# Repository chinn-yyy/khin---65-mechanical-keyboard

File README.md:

# khin---65-mechanical-keyboard
This keyboard was designed for productivity for the Blueprint club ran by HackClub. It features a 66 key layout with 2 programmable macro keys. I chose the MMD Fairy Linear switches for this project. Not only do they sound amazing, they also match my vibe; transparent. Additionally, I decided to use some random AliExpress screw-in stabilizers that are also, you guessed it, transparent! 

My keyboard isn't just a keyboard with keys. It also features a big, bright, 0.91 inch OLED display that can display the last key you pressed, a fun animation, etc. Not only does it have an OLED it also has 68 addressable LED's. One for each key. These can be any color and any pattern.

On the firmware side of things, my keyboard is being ran by QMK open source firmware on a Raspberry Pi Pico. QMK is specifically designed for keyboards, and not only is it easy to use but it also has tons of features. 

Make sure to look at my Blueprint page to see the journal and the process it took to build this. Here is the link: https://blueprint.hackclub.com/projects/11738

Here are some photos of the finished product:

  Fully Assembled (CAD):

  Schematic:

  PCB Editor:

  CAD:

[tableConvert.com_irgoez.md](https://github.com/user-attachments/files/25429461/tableConvert.com_irgoez.md)
| Name:                             | Description:                                                        | Price: (each) | Shipping Price: | Quanity: | Manufacturer: | Total Price (with tax + shipping): | URL:                                                                                                                                                                                                                                                                                                                                                                                                                                                                                                                                                                                                                                        |
|-----------------------------------|---------------------------------------------------------------------|---------------|-----------------|----------|---------------|------------------------------------|---------------------------------------------------------------------------------------------------------------------------------------------------------------------------------------------------------------------------------------------------------------------------------------------------------------------------------------------------------------------------------------------------------------------------------------------------------------------------------------------------------------------------------------------------------------------------------------------------------------------------------------------|
| Raspberry Pi Pico w/ Headers      | 40 pin RP2040 based MCU, the brains for the keyboard. (not the offical one, proceed with caution)               | $3.41         | $0.00           | 1        | AliExpress        | $3.94                              | https://www.aliexpress.us/item/3256805941727857.html?spm=a2g0o.cart.0.0.295b38daIYYoHW&mp=1&pdp_npi=6%40dis%21USD%21USD%203.41%21USD%203.41%21%21USD%203.41%21%21%21%402103212317738723428262562e918f%2112000035881956746%21ct%21US%216916366760%21%211%210%21&_gl=1*17auvbk*_gcl_aw*R0NMLjE3NzM2MDE5MDIuQ2owS0NRandzZG5OQmhDNEFSSXNBQV8zaGVpZ1R3cW5RcFRoUlY1S0hManNRUVdXY0pHMEVsM1UtMV96MlQ0YVdkZmw2VFkyaS05Qm5lY2FBc2RWRUFMd193Y0I.*_gcl_dc*R0NMLjE3NzM2MDE5MDIuQ2owS0NRandzZG5OQmhDNEFSSXNBQV8zaGVpZ1R3cW5RcFRoUlY1S0hManNRUVdXY0pHMEVsM1UtMV96MlQ0YVdkZmw2VFkyaS05Qm5lY2FBc2RWRUFMd193Y0I.*_gcl_au*MTkwNzg4MzkyMy4xNzY5MDMzMzcx*_ga*MjkyODU0MjIxLjE3NzM4NzE3NDY.*_ga_VED1YSGNC7*czE3NzM4NzE3NDUkbzEkZzEkdDE3NzM4NzIzNDMkajU5JGwwJGgw&gatewayAdapt=glo2usa                                                                                                                                                                                                                                                                                                                                                                                                                                                                                                                                                                        |
| V2 PCB Mount Screw-in Stabilizers | Keyboard stabilizers, allows the space, shift etc. to not collapse. | $5.27         | $0.00           | 1        | AliExpress    | $6.08                              | https://www.aliexpress.us/item/3256807050530252.html?spm=a2g0o.cart.0.0.1d1938daK18Quu&mp=1&pdp_npi=6%40dis%21USD%21USD%205.58%21USD%205.27%21%21USD%205.12%21%21%21%402101eecd17715431674755596e02ab%2112000039909995531%21ct%21US%216916366760%21%211%210%21&_gl=1*1gsy9e4*_gcl_aw*R0NMLjE3Njk4MDk2MjEuQ2p3S0NBaUFqOExMQmhBa0Vpd0FKamJZNzBrTW1QMW5Fa1VGM1F0RzFFLXI5amsxQnc4dU1UNko1MWo4V3RWZ24yM1doeGZNdXJseDZob0MxLVlRQXZEX0J3RQ..*_gcl_au*MTkwNzg4MzkyMy4xNzY5MDMzMzcx*_ga*Mzk1Mzc0NzMxLjE3NzE0NTE5NjM.*_ga_VED1YSGNC7*czE3NzE1NDMxMzIkbzMkZzEkdDE3NzE1NDMzMzckajQyJGwwJGgw&gatewayAdapt=glo2usa                                        |
| MMD Fairy Switch Linear           | Clear keyboard switches, buttons. Pack of 70.                       | $32.57        | $0.00           | 1        | AliExpress    | $37.59                             | https://www.aliexpress.us/item/3256805623892710.html?src=google&pdp_npi=4%40dis%21USD%2114.90%2113.71%21%21%21%21%21%40%2112000034431152527%21ppc%21%21%21&gatewayAdapt=glo2usa                                                                                                                                                                                                                                                                                                                                                                                                                                                             |
| 1N4148 Switching Diode            | Used in the keyboard matrix to prevent ghosting. Pack of 50.        | $1.23         | $0.00           | 2        | AliExpress    | $2.84                              | https://www.aliexpress.us/item/3256806058794623.html?spm=a2g0o.cart.0.0.1d1938daMNUGBd&mp=1&pdp_npi=6%40dis%21USD%21USD%201.79%21USD%201.23%21%21USD%201.07%21%21%21%402101eecd17713708062508328e02a6%2112000036448323916%21ct%21US%216916366760%21%212%210%21&_gl=1*5igzdr*_gcl_aw*R0NMLjE3Njk4MDk2MjEuQ2p3S0NBaUFqOExMQmhBa0Vpd0FKamJZNzBrTW1QMW5Fa1VGM1F0RzFFLXI5amsxQnc4dU1UNko1MWo4V3RWZ24yM1doeGZNdXJseDZob0MxLVlRQXZEX0J3RQ..*_gcl_au*MTkwNzg4MzkyMy4xNzY5MDMzMzcx*_ga*NDk1NTA1MDMwLjE3NzEzNjg0MzM.*_ga_VED1YSGNC7*czE3NzEzNjg0MzIkbzEkZzEkdDE3NzEzNzEwMTUkajU5JGwwJGgw&gatewayAdapt=glo2usa                                         |
| SK6812 MINI-E RGB                 | Addressable LED's for the keyboard. Pack of 100.                    | $6.03         | $0.00           | 1        | AliExpress    | $6.96                              | https://www.aliexpress.us/item/3256805007401420.html?spm=a2g0o.cart.0.0.1d1938daMNUGBd&mp=1&pdp_npi=6%40dis%21USD%21USD%206.42%21USD%206.03%21%21USD%205.32%21%21%21%402101eecd17713708062508328e02a6%2112000032072424635%21ct%21US%216916366760%21%211%210%21&_gl=1*5igzdr*_gcl_aw*R0NMLjE3Njk4MDk2MjEuQ2p3S0NBaUFqOExMQmhBa0Vpd0FKamJZNzBrTW1QMW5Fa1VGM1F0RzFFLXI5amsxQnc4dU1UNko1MWo4V3RWZ24yM1doeGZNdXJseDZob0MxLVlRQXZEX0J3RQ..*_gcl_au*MTkwNzg4MzkyMy4xNzY5MDMzMzcx*_ga*NDk1NTA1MDMwLjE3NzEzNjg0MzM.*_ga_VED1YSGNC7*czE3NzEzNjg0MzIkbzEkZzEkdDE3NzEzNzEwMTUkajU5JGwwJGgw&gatewayAdapt=glo2usa                                         |
| 0.91 inch OLED                    | 0.91 inch, 128x32, SSD1306, I2C, OLED display. (already have)       | $1.97         | $0.00           | 1        | AliExpress    | $0.00                              | https://www.aliexpress.us/item/3256805114690528.html?spm=a2g0o.productlist.main.33.508byZ3oyZ3oyT&algo_pvid=eb5a6790-e38d-4eb1-b34e-9abb2a502be0&algo_exp_id=eb5a6790-e38d-4eb1-b34e-9abb2a502be0-32&pdp_ext_f=%7B%22order%22%3A%222979%22%2C%22eval%22%3A%221%22%2C%22fromPage%22%3A%22search%22%7D&pdp_npi=6%40dis%21USD%211.97%211.97%21%21%211.97%211.97%21%402103212317713684409616193ef62c%2112000032548039884%21sea%21US%216916366760%21X%211%210%21n_tag%3A-29913%3Bd%3A729337c7%3Bm03_new_user%3A-29895&curPageLogUid=xd4wKAHaNW7A&utparam-url=scene%3Asearch%7Cquery_from%3A%7Cx_object_id%3A1005005301005280%7C_p_origin_prod%3A |
| Custom PCB                        | Custom printed circuit board, the foundation. (pack of 5)           | $17.60        | $12.97          | 1        | JLCPCB        | $33.28                             | https://jlcpcb.com/                                                                                                                                                                                                                                                                                                                                                                                                                                                                                                                                                                                                                         |
| TOTAL:                            |                                                                     |               |                 |          |               | $91.75                             | Link to Google Spreadsheet: https://docs.google.com/spreadsheets/d/17dnJcXFBqe7aWQwjPS5lmQD_NSss1hXRMHxMUS2wsAg/edit?usp=sharing                                                                                                                                                                                                                                                                                                                                                                                                                                                                                                            |

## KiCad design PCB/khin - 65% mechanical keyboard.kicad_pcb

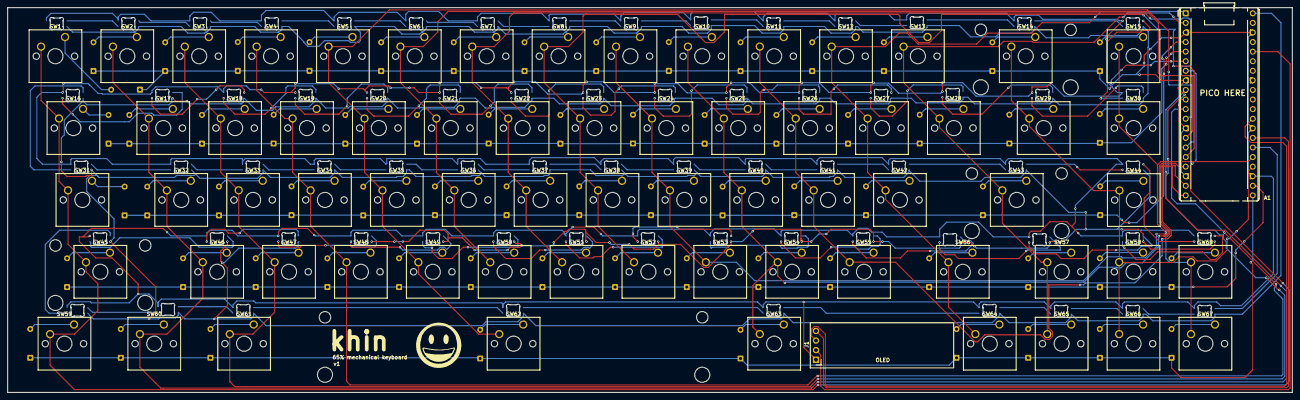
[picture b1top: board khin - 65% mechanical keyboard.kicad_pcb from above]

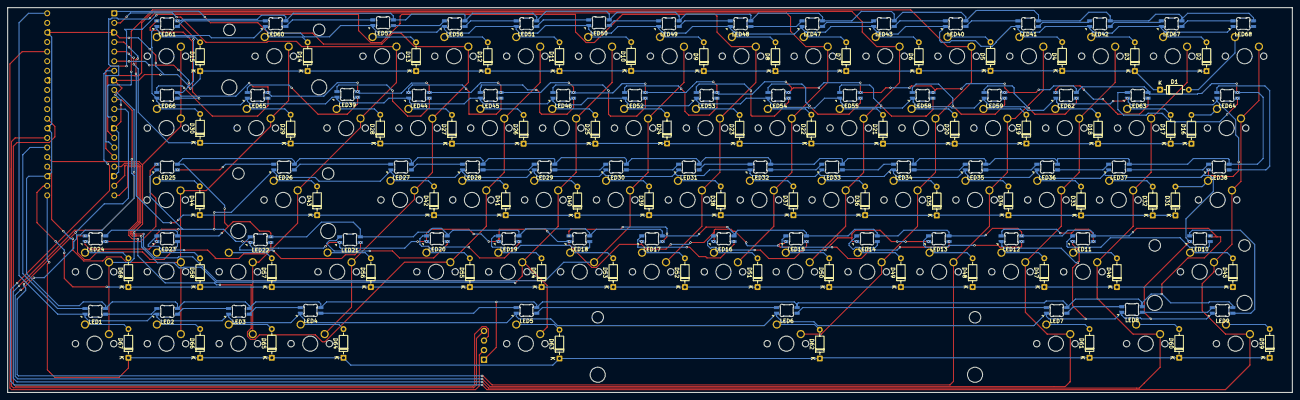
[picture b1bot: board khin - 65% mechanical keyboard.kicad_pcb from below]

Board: 2 copper layers, 340.5 x 102.0 mm, 206 parts (136 on the bottom side), 161 nets.

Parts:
A1: RaspberryPi_Pico; RaspberryPi_Pico_Common_THT
D1, D2, D3, D4, D5, D6, D7, D8, D9, D10, D11, D12, D13, D14, D15, D16, D17, D18, D19, D20, D21, D22, D23, D24, D25, D26, D27, D28, D29, D30, D31, D32, D33, D34, D35, D36, D37, D38, D39, D40, D41, D42, D43, D44, D45, D46, D47, D48, D49, D50, D51, D52, D53, D54, D55, D56, D57, D58, D59, D60, D61, D62, D63, D64, D65, D66, D67, D68: 1N4148; D_DO-35_SOD27_P7.62mm_Horizontal
J1: Conn_01x04_Pin; OLED_0.91_128x323D
LED1, LED2, LED3, LED4, LED5, LED6, LED7, LED8, LED9, LED10, LED11, LED12, LED13, LED14, LED15, LED16, LED17, LED18, LED19, LED20, LED21, LED22, LED23, LED24, LED25, LED26, LED27, LED28, LED29, LED30, LED31, LED32, LED33, LED34, LED35, LED36, LED37, LED38, LED39, LED40, LED41, LED42, LED43, LED44, LED45, LED46, LED47, LED48, LED49, LED50, LED51, LED52, LED53, LED54, LED55, LED56, LED57, LED58, LED59, LED60, LED61, LED62, LED63, LED64, LED65, LED66, LED67, LED68: MX_SK6812MINI-E; LED_6028R
SW1: SW_Push-ESC; SW_Cherry_MX_1.00u_PCB3D
SW2: SW_Push-1; SW_Cherry_MX_1.00u_PCB3D
SW3: SW_Push-2; SW_Cherry_MX_1.00u_PCB3D
SW4: SW_Push-3; SW_Cherry_MX_1.00u_PCB3D
SW5: SW_Push-4; SW_Cherry_MX_1.00u_PCB3D
SW6: SW_Push-5; SW_Cherry_MX_1.00u_PCB3D
SW7: SW_Push-6; SW_Cherry_MX_1.00u_PCB3D
SW8: SW_Push-7; SW_Cherry_MX_1.00u_PCB3D
SW9: SW_Push-8; SW_Cherry_MX_1.00u_PCB3D
SW10: SW_Push-9; SW_Cherry_MX_1.00u_PCB3D
SW11: SW_Push-0; SW_Cherry_MX_1.00u_PCB3D
SW12: SW_Push-dash; SW_Cherry_MX_1.00u_PCB3D
SW13: SW_Push-=; SW_Cherry_MX_1.00u_PCB3D
SW14: SW_Push-BS; SW_Cherry_MX_2.00u_PCB3D+Stabilizers
SW15: SW_Push-DEL; SW_Cherry_MX_1.00u_PCB3D
SW16: SW_Push-TAB; SW_Cherry_MX_1.50u_PCB3D
SW17: SW_Push-Q; SW_Cherry_MX_1.00u_PCB3D
SW18: SW_Push-W; SW_Cherry_MX_1.00u_PCB3D
SW19: SW_Push-E; SW_Cherry_MX_1.00u_PCB3D
SW20: SW_Push-R; SW_Cherry_MX_1.00u_PCB3D
SW21: SW_Push-T; SW_Cherry_MX_1.00u_PCB3D
SW22: SW_Push-Y; SW_Cherry_MX_1.00u_PCB3D
SW23: SW_Push-U; SW_Cherry_MX_1.00u_PCB3D
SW24: SW_Push-I; SW_Cherry_MX_1.00u_PCB3D
SW25: SW_Push-O; SW_Cherry_MX_1.00u_PCB3D
SW26: SW_Push-P; SW_Cherry_MX_1.00u_PCB3D
SW27: SW_Push-[; SW_Cherry_MX_1.00u_PCB3D
SW28: SW_Push-]; SW_Cherry_MX_1.00u_PCB3D
SW29: SW_Push-\; SW_Cherry_MX_1.50u_PCB3D
SW30: SW_Push-PAS; SW_Cherry_MX_1.00u_PCB3D
SW31: SW_Push-CL; SW_Cherry_MX_1.75u_PCB3D
SW32: SW_Push-A; SW_Cherry_MX_1.00u_PCB3D
SW33: SW_Push-S; SW_Cherry_MX_1.00u_PCB3D
SW34: SW_Push-D; SW_Cherry_MX_1.00u_PCB3D
SW35: SW_Push-F; SW_Cherry_MX_1.00u_PCB3D
SW36: SW_Push-G; SW_Cherry_MX_1.00u_PCB3D
SW37: SW_Push-H; SW_Cherry_MX_1.00u_PCB3D
SW38: SW_Push-J; SW_Cherry_MX_1.00u_PCB3D
SW39: SW_Push-K; SW_Cherry_MX_1.00u_PCB3D
SW40: SW_Push-L; SW_Cherry_MX_1.00u_PCB3D
SW41: SW_Push-;; SW_Cherry_MX_1.00u_PCB3D
SW42: SW_Push-'; SW_Cherry_MX_1.00u_PCB3D
SW43: SW_Push-EN; SW_Cherry_MX_2.25u_PCB3D+Stabilizer
SW44: SW_Push-LM; SW_Cherry_MX_1.00u_PCB3D
SW45: SW_Push-LSH; SW_Cherry_MX_2.25u_PCB3D+Stabilizer
SW46: SW_Push-Z; SW_Cherry_MX_1.00u_PCB3D
SW47: SW_Push-X; SW_Cherry_MX_1.00u_PCB3D
SW48: SW_Push-C; SW_Cherry_MX_1.00u_PCB3D
SW49: SW_Push-V; SW_Cherry_MX_1.00u_PCB3D
SW50: SW_Push-B; SW_Cherry_MX_1.00u_PCB3D
SW51: SW_Push-N; SW_Cherry_MX_1.00u_PCB3D
SW52: SW_Push-M; SW_Cherry_MX_1.00u_PCB3D
SW53: SW_Push-,; SW_Cherry_MX_1.00u_PCB3D
SW54: SW_Push-.; SW_Cherry_MX_1.00u_PCB3D
SW55: SW_Push-/; SW_Cherry_MX_1.00u_PCB3D
SW56: SW_Push-RSH; SW_Cherry_MX_1.75u_PCB3D
SW57: SW_Push-UPA; SW_Cherry_MX_1.00u_PCB3D
SW58: SW_Push-MODE; SW_Cherry_MX_1.00u_PCB3D
SW59: SW_Push-LCTL; SW_Cherry_MX_1.25u_PCB3D
SW60: SW_Push-WIN; SW_Cherry_MX_1.25u_PCB3D
SW61: SW_Push-LALT; SW_Cherry_MX_1.25u_PCB3D
SW62: SW_Push-SP; SW_Cherry_MX_6.25u_PCB3D
SW63: SW_Push-RCTL; SW_Cherry_MX_1.00u_PCB3D
SW64: SW_Push-LA; SW_Cherry_MX_1.00u_PCB3D
SW65: SW_Push-DA; SW_Cherry_MX_1.00u_PCB3D
SW66: SW_Push-RA; SW_Cherry_MX_1.00u_PCB3D
SW67: SW_Push-M2; SW_Cherry_MX_1.00u_PCB3D
SW68: SW_Push-M1; SW_Cherry_MX_1.00u_PCB3D

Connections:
+3V3: A1.36 (3V3), J1.2
+5V: A1.40 (VBUS), LED1.4 (VSS), LED2.4 (VSS), LED3.4 (VSS), LED4.4 (VSS), LED5.4 (VSS), LED6.4 (VSS), LED7.4 (VSS), LED8.4 (VSS), LED9.4 (VSS), LED10.4 (VSS), LED11.4 (VSS), LED12.4 (VSS), LED13.4 (VSS), LED14.4 (VSS), LED15.4 (VSS), LED16.4 (VSS), LED17.4 (VSS), LED18.4 (VSS), LED19.4 (VSS), LED20.4 (VSS), LED21.4 (VSS), LED22.4 (VSS), LED23.4 (VSS), LED24.4 (VSS), LED25.4 (VSS), LED26.4 (VSS), LED27.4 (VSS), LED28.4 (VSS), LED29.4 (VSS), LED30.4 (VSS), LED31.4 (VSS), LED32.4 (VSS), LED33.4 (VSS), LED34.4 (VSS), LED35.4 (VSS), LED36.4 (VSS), LED37.4 (VSS), LED38.4 (VSS), LED39.4 (VSS), LED40.4 (VSS), LED41.4 (VSS), LED42.4 (VSS), LED43.4 (VSS), LED44.4 (VSS), LED45.4 (VSS), LED46.4 (VSS), LED47.4 (VSS), LED48.4 (VSS), LED49.4 (VSS), LED50.4 (VSS), LED51.4 (VSS), LED52.4 (VSS), LED53.4 (VSS), LED54.4 (VSS), LED55.4 (VSS), LED56.4 (VSS), LED57.4 (VSS), LED58.4 (VSS), LED59.4 (VSS), LED60.4 (VSS), LED61.4 (VSS), LED62.4 (VSS), LED63.4 (VSS), LED64.4 (VSS), LED65.4 (VSS), LED66.4 (VSS), LED67.4 (VSS), LED68.4 (VSS)
Col 0: A1.7 (GPIO5), SW1.2, SW16.2, SW31.2, SW45.2, SW59.2
Col 1: A1.9 (GPIO6), SW2.2, SW17.2, SW32.2, SW46.2, SW60.2
Col 2: A1.10 (GPIO7), SW3.2, SW18.2, SW33.2, SW47.2, SW61.2
Col 3: A1.11 (GPIO8), SW4.2, SW19.2, SW34.2, SW48.2
Col 4: A1.12 (GPIO9), SW5.2, SW20.2, SW35.2, SW49.2, SW62.2
Col 5: A1.14 (GPIO10), SW6.2, SW21.2, SW36.2, SW50.2
Col 6: A1.15 (GPIO11), SW7.2, SW22.2, SW37.2, SW51.2
Col 7: A1.16 (GPIO12), SW8.2, SW23.2, SW38.2, SW52.2
Col 8: A1.17 (GPIO13), SW9.2, SW24.2, SW39.2, SW53.2
Col 9: A1.19 (GPIO14), SW10.2, SW25.2, SW40.2, SW54.2, SW63.2
Col 10: A1.20 (GPIO15), SW11.2, SW26.2, SW41.2, SW55.2
Col 11: A1.1 (GPIO0), SW12.2, SW27.2, SW42.2, SW56.2, SW64.2
Col 12: A1.2 (GPIO1), SW13.2, SW28.2, SW43.2, SW57.2, SW65.2
Col 13: A1.24 (GPIO18), SW14.2, SW29.2, SW44.2, SW58.2, SW66.2
Col 14: A1.25 (GPIO19), SW15.2, SW30.2, SW67.2, SW68.2
GND: A1.3 (GND), A1.8 (GND), A1.13 (GND), A1.18 (GND), A1.23 (GND), A1.28 (GND), A1.38 (GND), J1.1, LED1.1 (VDD), LED2.1 (VDD), LED3.1 (VDD), LED4.1 (VDD), LED5.1 (VDD), LED6.1 (VDD), LED7.1 (VDD), LED8.1 (VDD), LED9.1 (VDD), LED10.1 (VDD), LED11.1 (VDD), LED12.1 (VDD), LED13.1 (VDD), LED14.1 (VDD), LED15.1 (VDD), LED16.1 (VDD), LED17.1 (VDD), LED18.1 (VDD), LED19.1 (VDD), LED20.1 (VDD), LED21.1 (VDD), LED22.1 (VDD), LED23.1 (VDD), LED24.1 (VDD), LED25.1 (VDD), LED26.1 (VDD), LED27.1 (VDD), LED28.1 (VDD), LED29.1 (VDD), LED30.1 (VDD), LED31.1 (VDD), LED32.1 (VDD), LED33.1 (VDD), LED34.1 (VDD), LED35.1 (VDD), LED36.1 (VDD), LED37.1 (VDD), LED38.1 (VDD), LED39.1 (VDD), LED40.1 (VDD), LED41.1 (VDD), LED42.1 (VDD), LED43.1 (VDD), LED44.1 (VDD), LED45.1 (VDD), LED46.1 (VDD), LED47.1 (VDD), LED48.1 (VDD), LED49.1 (VDD), LED50.1 (VDD), LED51.1 (VDD), LED52.1 (VDD), LED53.1 (VDD), LED54.1 (VDD), LED55.1 (VDD), LED56.1 (VDD), LED57.1 (VDD), LED58.1 (VDD), LED59.1 (VDD), LED60.1 (VDD), LED61.1 (VDD), LED62.1 (VDD), LED63.1 (VDD), LED64.1 (VDD), LED65.1 (VDD), LED66.1 (VDD), LED67.1 (VDD), LED68.1 (VDD)
LED: A1.26 (GPIO20), LED1.3 (DIN)
LED ROW 1 TO ROW 2: LED12.2 (DOUT), LED13.3 (DIN)
LED ROW 2 TO ROW 3: LED25.2 (DOUT), LED26.3 (DIN)
LED ROW 3 TO ROW 4: LED38.2 (DOUT), LED64.3 (DIN)
LED ROW 4 TO ROW 5: LED39.2 (DOUT), LED65.3 (DIN)
unnamed: D1.2 (A), SW1.1
unnamed: D2.2 (A), SW2.1
unnamed: D3.2 (A), SW3.1
unnamed: D4.2 (A), SW4.1
unnamed: D5.2 (A), SW5.1
unnamed: D6.2 (A), SW6.1
unnamed: D7.2 (A), SW7.1
unnamed: D8.2 (A), SW8.1
unnamed: D9.2 (A), SW9.1
unnamed: D10.2 (A), SW10.1
unnamed: D11.2 (A), SW11.1
unnamed: D12.2 (A), SW12.1
unnamed: D13.2 (A), SW13.1
unnamed: D14.2 (A), SW14.1
unnamed: D15.2 (A), SW15.1
unnamed: D16.2 (A), SW16.1
unnamed: D17.2 (A), SW17.1
unnamed: D18.2 (A), SW18.1
unnamed: D19.2 (A), SW19.1
unnamed: D20.2 (A), SW20.1
unnamed: D21.2 (A), SW21.1
unnamed: D22.2 (A), SW22.1
unnamed: D23.2 (A), SW23.1
unnamed: D24.2 (A), SW24.1
unnamed: D25.2 (A), SW25.1
unnamed: D26.2 (A), SW26.1
unnamed: D27.2 (A), SW27.1
unnamed: D28.2 (A), SW28.1
unnamed: D29.2 (A), SW29.1
unnamed: D30.2 (A), SW30.1
unnamed: D31.2 (A), SW31.1
unnamed: D32.2 (A), SW32.1
unnamed: D33.2 (A), SW33.1
unnamed: D34.2 (A), SW34.1
unnamed: D35.2 (A), SW35.1
unnamed: D36.2 (A), SW36.1
unnamed: D37.2 (A), SW37.1
unnamed: D38.2 (A), SW38.1
unnamed: D39.2 (A), SW39.1
unnamed: D40.2 (A), SW40.1
unnamed: D41.2 (A), SW41.1
unnamed: D42.2 (A), SW42.1
unnamed: D43.2 (A), SW43.1
unnamed: D44.2 (A), SW44.1
unnamed: D45.2 (A), SW45.1
unnamed: D46.2 (A), SW46.1
unnamed: D47.2 (A), SW47.1
unnamed: D48.2 (A), SW48.1
unnamed: D49.2 (A), SW49.1
unnamed: D50.2 (A), SW50.1
unnamed: D51.2 (A), SW51.1
unnamed: D52.2 (A), SW52.1
unnamed: D53.2 (A), SW53.1
unnamed: D54.2 (A), SW54.1
unnamed: D55.2 (A), SW55.1
unnamed: D56.2 (A), SW56.1
unnamed: D57.2 (A), SW57.1
unnamed: D58.2 (A), SW58.1
unnamed: D59.2 (A), SW59.1
unnamed: D60.2 (A), SW60.1
unnamed: D61.2 (A), SW61.1
unnamed: D62.2 (A), SW62.1
unnamed: D63.2 (A), SW63.1
unnamed: D64.2 (A), SW64.1
unnamed: D65.2 (A), SW65.1
unnamed: D66.2 (A), SW66.1
unnamed: D67.2 (A), SW67.1
unnamed: D68.2 (A), SW68.1
unnamed: LED1.2 (DOUT), LED2.3 (DIN)
unnamed: LED2.2 (DOUT), LED3.3 (DIN)
unnamed: LED3.2 (DOUT), LED4.3 (DIN)
unnamed: LED4.2 (DOUT), LED5.3 (DIN)
unnamed: LED5.2 (DOUT), LED6.3 (DIN)
unnamed: LED6.2 (DOUT), LED7.3 (DIN)
unnamed: LED7.2 (DOUT), LED8.3 (DIN)
unnamed: LED8.2 (DOUT), LED9.3 (DIN)
unnamed: LED9.2 (DOUT), LED10.3 (DIN)
unnamed: LED10.2 (DOUT), LED11.3 (DIN)
unnamed: LED11.2 (DOUT), LED12.3 (DIN)
unnamed: LED13.2 (DOUT), LED14.3 (DIN)
unnamed: LED14.2 (DOUT), LED15.3 (DIN)
unnamed: LED15.2 (DOUT), LED16.3 (DIN)
unnamed: LED16.2 (DOUT), LED17.3 (DIN)
unnamed: LED17.2 (DOUT), LED18.3 (DIN)
unnamed: LED18.2 (DOUT), LED19.3 (DIN)
unnamed: LED19.2 (DOUT), LED20.3 (DIN)
unnamed: LED20.2 (DOUT), LED21.3 (DIN)
unnamed: LED21.2 (DOUT), LED22.3 (DIN)
unnamed: LED22.2 (DOUT), LED23.3 (DIN)
unnamed: LED23.2 (DOUT), LED24.3 (DIN)
unnamed: LED24.2 (DOUT), LED25.3 (DIN)
unnamed: LED26.2 (DOUT), LED27.3 (DIN)
unnamed: LED27.2 (DOUT), LED28.3 (DIN)
unnamed: LED28.2 (DOUT), LED29.3 (DIN)
unnamed: LED29.2 (DOUT), LED30.3 (DIN)
unnamed: LED30.2 (DOUT), LED31.3 (DIN)
unnamed: LED31.2 (DOUT), LED32.3 (DIN)
unnamed: LED32.2 (DOUT), LED33.3 (DIN)
unnamed: LED33.2 (DOUT), LED34.3 (DIN)
unnamed: LED34.2 (DOUT), LED35.3 (DIN)
unnamed: LED35.2 (DOUT), LED36.3 (DIN)
unnamed: LED36.2 (DOUT), LED37.3 (DIN)
unnamed: LED37.2 (DOUT), LED38.3 (DIN)
unnamed: LED39.3 (DIN), LED44.2 (DOUT)
unnamed: LED40.3 (DIN), LED43.2 (DOUT)
unnamed: LED40.2 (DOUT), LED41.3 (DIN)
unnamed: LED41.2 (DOUT), LED42.3 (DIN)
unnamed: LED42.2 (DOUT), LED67.3 (DIN)
unnamed: LED43.3 (DIN), LED47.2 (DOUT)
unnamed: LED44.3 (DIN), LED45.2 (DOUT)
unnamed: LED45.3 (DIN), LED46.2 (DOUT)
unnamed: LED46.3 (DIN), LED52.2 (DOUT)
unnamed: LED47.3 (DIN), LED48.2 (DOUT)
unnamed: LED48.3 (DIN), LED49.2 (DOUT)
unnamed: LED49.3 (DIN), LED50.2 (DOUT)
unnamed: LED50.3 (DIN), LED51.2 (DOUT)
unnamed: LED51.3 (DIN), LED56.2 (DOUT)
unnamed: LED52.3 (DIN), LED53.2 (DOUT)
unnamed: LED53.3 (DIN), LED54.2 (DOUT)
unnamed: LED54.3 (DIN), LED55.2 (DOUT)
unnamed: LED55.3 (DIN), LED58.2 (DOUT)
unnamed: LED56.3 (DIN), LED57.2 (DOUT)
unnamed: LED57.3 (DIN), LED60.2 (DOUT)
unnamed: LED58.3 (DIN), LED59.2 (DOUT)
unnamed: LED59.3 (DIN), LED62.2 (DOUT)
unnamed: LED60.3 (DIN), LED61.2 (DOUT)
unnamed: LED61.3 (DIN), LED66.2 (DOUT)
unnamed: LED62.3 (DIN), LED63.2 (DOUT)
unnamed: LED63.3 (DIN), LED64.2 (DOUT)
unnamed: LED65.2 (DOUT), LED66.3 (DIN)
unnamed: LED67.2 (DOUT), LED68.3 (DIN)
Row 0: A1.6 (GPIO4), D1.1 (K), D2.1 (K), D3.1 (K), D4.1 (K), D5.1 (K), D6.1 (K), D7.1 (K), D8.1 (K), D9.1 (K), D10.1 (K), D11.1 (K), D12.1 (K), D13.1 (K), D14.1 (K), D15.1 (K)
Row 1: A1.5 (GPIO3), D16.1 (K), D17.1 (K), D18.1 (K), D19.1 (K), D20.1 (K), D21.1 (K), D22.1 (K), D23.1 (K), D24.1 (K), D25.1 (K), D26.1 (K), D27.1 (K), D28.1 (K), D29.1 (K), D30.1 (K)
Row 2: A1.4 (GPIO2), D31.1 (K), D32.1 (K), D33.1 (K), D34.1 (K), D35.1 (K), D36.1 (K), D37.1 (K), D38.1 (K), D39.1 (K), D40.1 (K), D41.1 (K), D42.1 (K), D43.1 (K), D44.1 (K)
Row 3: A1.22 (GPIO17), D45.1 (K), D46.1 (K), D47.1 (K), D48.1 (K), D49.1 (K), D50.1 (K), D51.1 (K), D52.1 (K), D53.1 (K), D54.1 (K), D55.1 (K), D56.1 (K), D57.1 (K), D58.1 (K), D68.1 (K)
Row 4: A1.21 (GPIO16), D59.1 (K), D60.1 (K), D61.1 (K), D62.1 (K), D63.1 (K), D64.1 (K), D65.1 (K), D66.1 (K), D67.1 (K)
SCL - OLED 1: A1.27 (GPIO21), J1.4
SDA - OLED 2: A1.29 (GPIO22), J1.3

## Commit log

2026-02-10 Create GOOGLE SPREADSHEET LINK
2026-02-10 Update and rename khin - BOM - Sheet1.csv to COMMA SEPERATED VALUES BOM
2026-02-17 Create PLACEHOLDER
2026-02-17 Rename khin - 65% mechanical keyboard.f3z to khin - 65% mechanical keyboard (fully assembled).f3z
2026-02-17 Create PLACHOLDER
2026-02-20 Update README.md images
2026-03-18 Rename khin - 65% mechanical keyboardv2.step to khin - 65% mechanical keyboard MAIN.step
2026-03-18 Rename khin - 65% mechanical keyboardv2-fusion.f3z to khin - 65% mechanical keyboardMAIN-FUSION.f3z
2026-03-20 Rename khin - 65 mechanical keyboard.zip to khin - 65 mechanical keyboard-PRODUCTION FILES.zip
